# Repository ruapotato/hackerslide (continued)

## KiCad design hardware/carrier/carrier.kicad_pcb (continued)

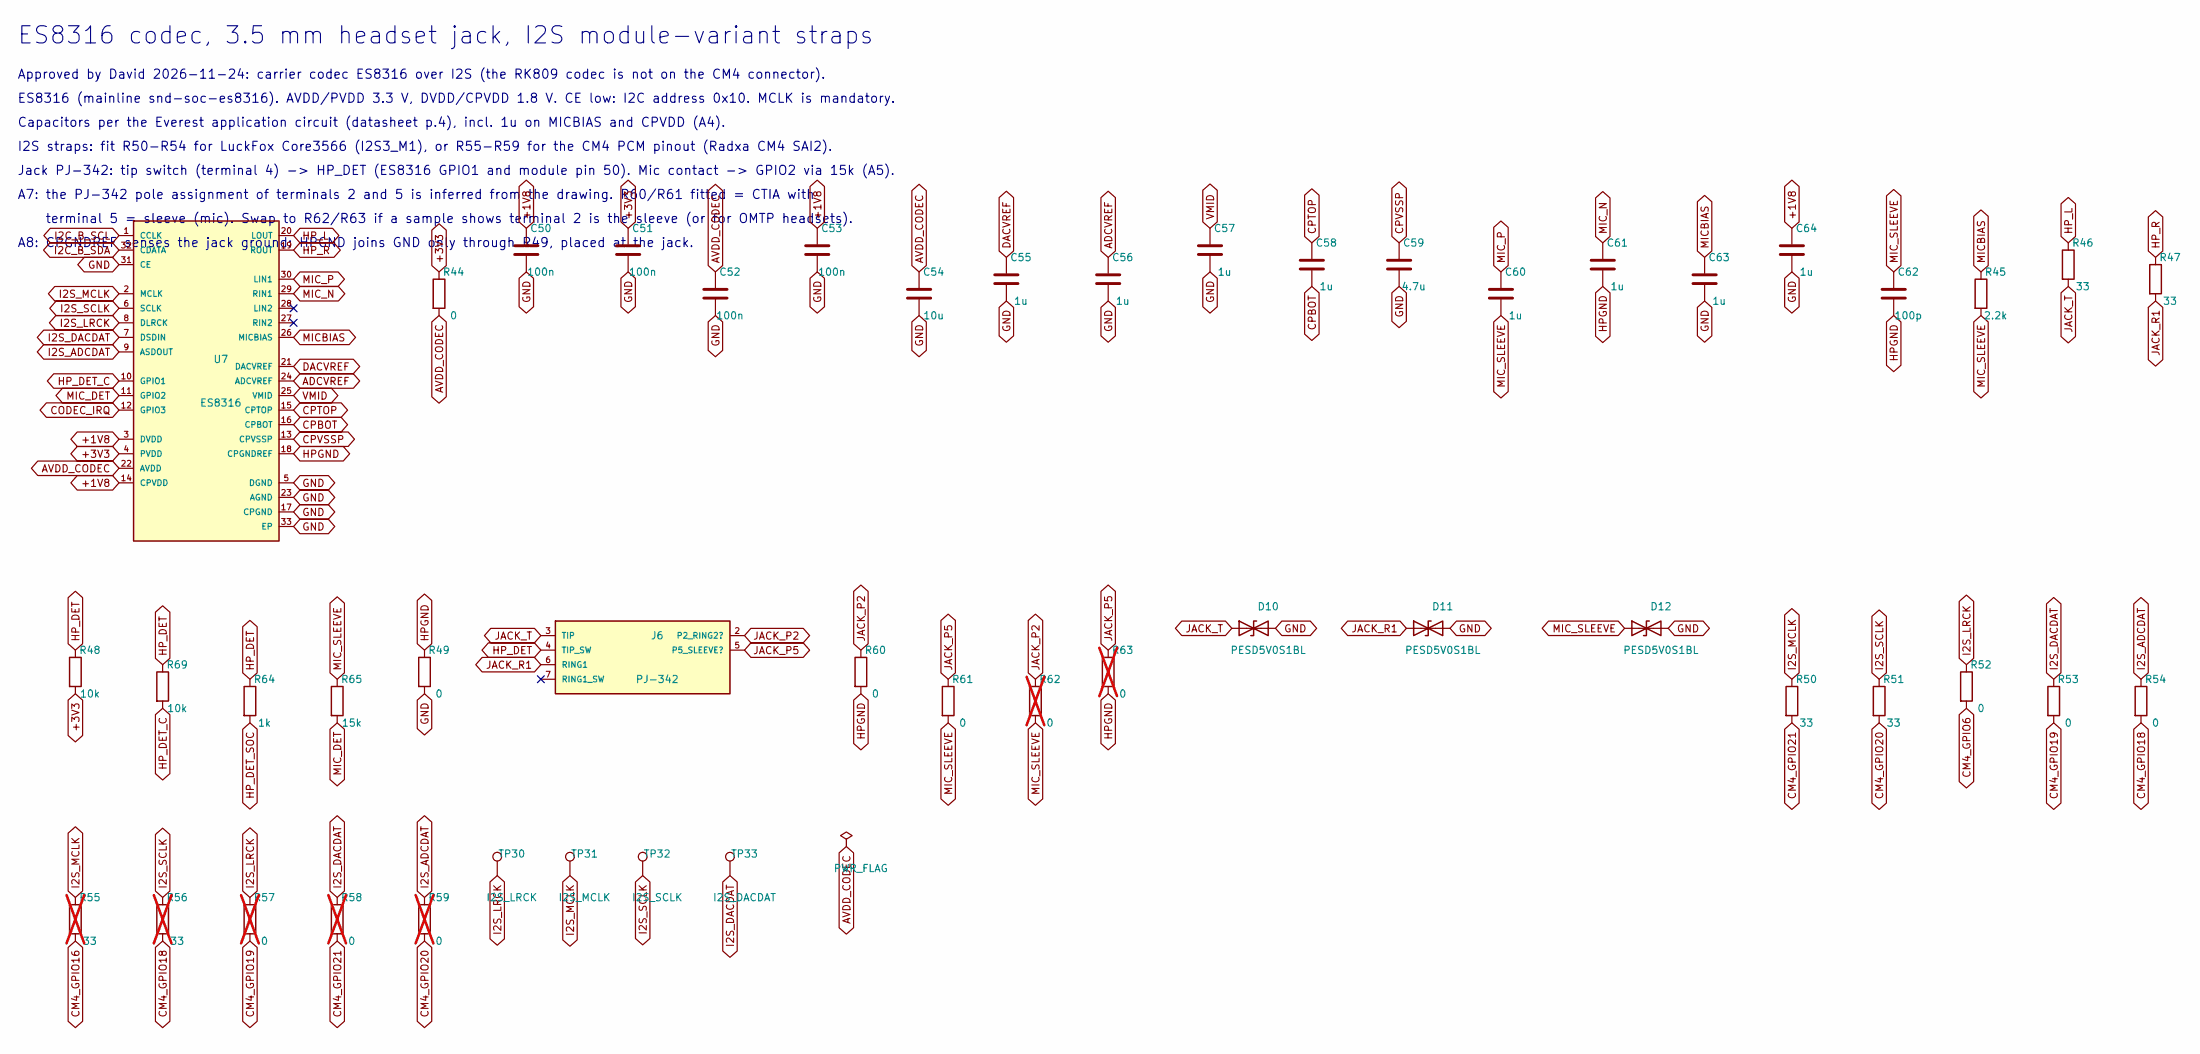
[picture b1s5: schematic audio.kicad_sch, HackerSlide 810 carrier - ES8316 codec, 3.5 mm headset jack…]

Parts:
C50, C51, C52, C53: 100n; C_0402_1005Metric; MPN CL05B104KO5NNNC; LCSC C1525
C54: 10u; C_0603_1608Metric; MPN CL10A106KP8NNNC; LCSC C19702
C55, C56, C57, C58, C60, C61, C63, C64: 1u; C_0402_1005Metric; MPN CL05A105KA5NQNC; LCSC C52923
C59: 4.7u; C_0402_1005Metric; MPN CL05A475MP5NRNC; LCSC C23733
C62: 100p; C_0402_1005Metric; MPN 0402CG101J500NT; LCSC C1546
D10, D11, D12: PESD5V0S1BL; D_SOD-882; MPN PESD5V0S1BL,315; LCSC C84374
J6: PJ-342; Jack_3.5mm_SHOUHAN_PJ-342; MPN PJ-342; LCSC C668606
R44, R49, R52, R53, R54, R60, R61: 0; R_0402_1005Metric; MPN 0402WGF0000TCE; LCSC C17168
R45: 2.2k; R_0402_1005Metric; MPN 0402WGF2201TCE; LCSC C25879
R46, R47, R50, R51: 33; R_0402_1005Metric; MPN 0402WGF330JTCE; LCSC C25105
R48, R69: 10k; R_0402_1005Metric; MPN 0402WGF1002TCE; LCSC C25744
R55, R56: 33; R_0402_1005Metric; MPN 0402WGF330JTCE; LCSC C25105; not fitted
R57, R58, R59, R62, R63: 0; R_0402_1005Metric; MPN 0402WGF0000TCE; LCSC C17168; not fitted
R64: 1k; R_0402_1005Metric; MPN 0402WGF1001TCE; LCSC C11702
R65: 15k; R_0402_1005Metric; MPN 0402WGF1502TCE; LCSC C25756
TP30: I2S_LRCK; TestPoint_Pad_D1.0mm
TP31: I2S_MCLK; TestPoint_Pad_D1.0mm
TP32: I2S_SCLK; TestPoint_Pad_D1.0mm
TP33: I2S_DACDAT; TestPoint_Pad_D1.0mm
U7: ES8316; VQFN-32-1EP_4x4mm_P0.4mm_EP2.8x2.8mm; MPN ES8316; LCSC C365735

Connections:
+1V8: C50.1, C53.1, C64.1, U7.3 (DVDD), U7.14 (CPVDD); also elsewhere on the board
+3V3: C51.1, R44.1, R48.2, U7.4 (PVDD); also elsewhere on the board
ADCVREF: C56.1, U7.24 (ADCVREF)
AVDD_CODEC: C52.1, C54.1, R44.2, U7.22 (AVDD)
CM4_GPIO6: R52.2; also elsewhere on the board
CM4_GPIO16: R55.2; also elsewhere on the board
CM4_GPIO18: R54.2, R56.2; also elsewhere on the board
CM4_GPIO19: R53.2, R57.2; also elsewhere on the board
CM4_GPIO20: R51.2, R59.2; also elsewhere on the board
CM4_GPIO21: R50.2, R58.2; also elsewhere on the board
CODEC_IRQ: U7.12 (GPIO3); also elsewhere on the board
CPBOT: C58.2, U7.16 (CPBOT)
CPTOP: C58.1, U7.15 (CPTOP)
CPVSSP: C59.1, U7.13 (CPVSSP)
DACVREF: C55.1, U7.21 (DACVREF)
GND: C50.2, C51.2, C52.2, C53.2, C54.2, C55.2, C56.2, C57.2, C59.2, C63.2, C64.2, D10.2 (A2), D11.2 (A2), D12.2 (A2), R49.2, U7.5 (DGND), U7.17 (CPGND), U7.23 (AGND), U7.31 (CE), U7.33 (EP); also elsewhere on the board
HPGND: C61.2, C62.2, R49.1, R60.2, R63.2, U7.18 (CPGNDREF)
HP_DET: J6.4 (TIP_SW), R48.1, R64.1, R69.1
HP_DET_C: R69.2, U7.10 (GPIO1)
HP_DET_SOC: R64.2; also elsewhere on the board
HP_L: R46.1, U7.20 (LOUT)
HP_R: R47.1, U7.19 (ROUT)
I2C_B_SCL: U7.1 (CCLK); also elsewhere on the board
I2C_B_SDA: U7.32 (CDATA); also elsewhere on the board
I2S_ADCDAT: R54.1, R59.1, U7.9 (ASDOUT)
I2S_DACDAT: R53.1, R58.1, TP33.1, U7.7 (DSDIN)
I2S_LRCK: R52.1, R57.1, TP30.1, U7.8 (DLRCK)
I2S_MCLK: R50.1, R55.1, TP31.1, U7.2 (MCLK)
I2S_SCLK: R51.1, R56.1, TP32.1, U7.6 (SCLK)
JACK_P2: J6.2 (P2_RING2?), R60.1, R62.1
JACK_P5: J6.5 (P5_SLEEVE?), R61.1, R63.1
JACK_R1: D11.1 (A1), J6.6 (RING1), R47.2
JACK_T: D10.1 (A1), J6.3 (TIP), R46.2
MICBIAS: C63.1, R45.1, U7.26 (MICBIAS)
MIC_DET: R65.2, U7.11 (GPIO2)
MIC_N: C61.1, U7.29 (RIN1)
MIC_P: C60.1, U7.30 (LIN1)
MIC_SLEEVE: C60.2, C62.1, D12.1 (A1), R45.2, R61.2, R62.2, R65.1
VMID: C57.1, U7.25 (VMID)

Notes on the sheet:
ES8316 codec, 3.5 mm headset jack, I2S module-variant straps
Approved by David 2026-11-24: carrier codec ES8316 over I2S (the RK809 codec is not on the CM4 connector).
ES8316 (mainline snd-soc-es8316). AVDD/PVDD 3.3 V, DVDD/CPVDD 1.8 V. CE low: I2C address 0x10. MCLK is mandatory.
Capacitors per the Everest application circuit (datasheet p.4), incl. 1u on MICBIAS and CPVDD (A4).
I2S straps: fit R50-R54 for LuckFox Core3566 (I2S3_M1), or R55-R59 for the CM4 PCM pinout (Radxa CM4 SAI2).
Jack PJ-342: tip switch (terminal 4) -> HP_DET (ES8316 GPIO1 and module pin 50). Mic contact -> GPIO2 via 15k (A5).
A7: the PJ-342 pole assignment of terminals 2 and 5 is inferred from the drawing. R60/R61 fitted = CTIA with
terminal 5 = sleeve (mic). Swap to R62/R63 if a sample shows terminal 2 is the sleeve (or for OMTP headsets).
A8: CPGNDREF senses the jack ground: HPGND joins GND only through R49, placed at the jack.

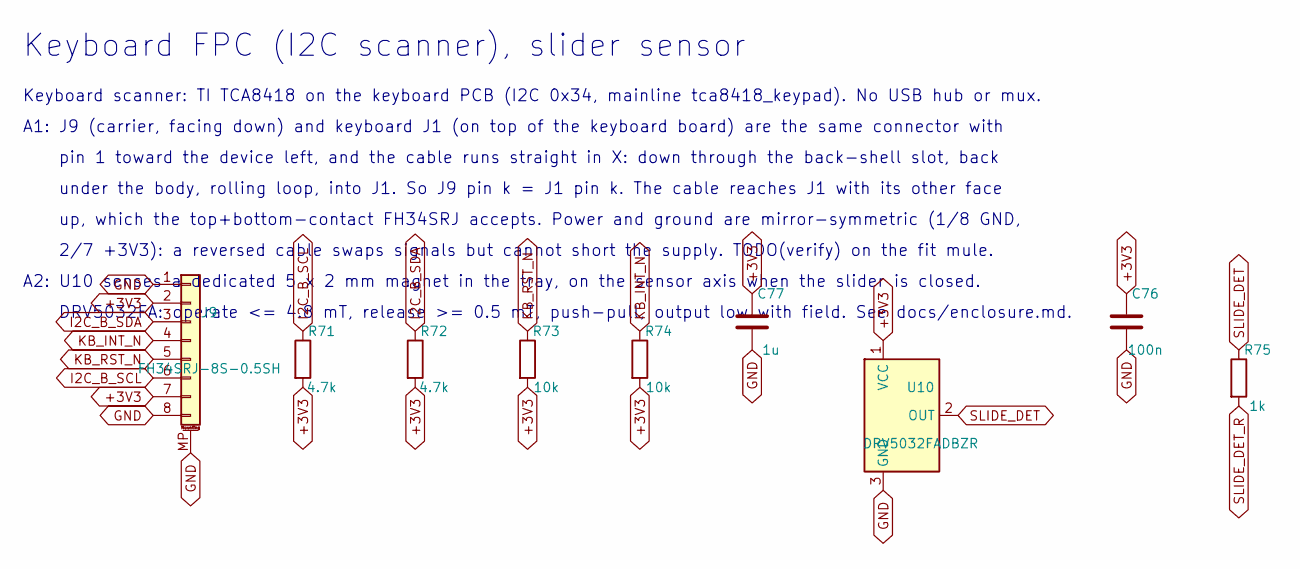
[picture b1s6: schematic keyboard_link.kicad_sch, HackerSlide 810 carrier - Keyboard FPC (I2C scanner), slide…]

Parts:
C76: 100n; C_0402_1005Metric; MPN CL05B104KO5NNNC; LCSC C1525
C77: 1u; C_0402_1005Metric; MPN CL05A105KA5NQNC; LCSC C52923
J9: FH34SRJ-8S-0.5SH; Hirose_FH34SRJ-8S-0.5SH_1x08-1MP_P0.50mm_Horizontal; MPN FH34SRJ-8S-0.5SH(50); LCSC C88372
R71, R72: 4.7k; R_0402_1005Metric; MPN 0402WGF4701TCE; LCSC C25900
R73, R74: 10k; R_0402_1005Metric; MPN 0402WGF1002TCE; LCSC C25744
R75: 1k; R_0402_1005Metric; MPN 0402WGF1001TCE; LCSC C11702
U10: DRV5032FADBZR; SOT-23; MPN DRV5032FADBZR; LCSC C140921

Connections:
+3V3: C76.1, C77.1, J9.2, J9.7, R71.2, R72.2, R73.2, R74.2, U10.1 (VCC); also elsewhere on the board
GND: C76.2, C77.2, J9.1, J9.8, J9.MP (MountPin), U10.3 (GND); also elsewhere on the board
I2C_B_SCL: J9.6, R71.1; also elsewhere on the board
I2C_B_SDA: J9.3, R72.1; also elsewhere on the board
KB_INT_N: J9.4, R74.1; also elsewhere on the board
KB_RST_N: J9.5, R73.1; also elsewhere on the board
SLIDE_DET: R75.1, U10.2 (OUT)
SLIDE_DET_R: R75.2; also elsewhere on the board

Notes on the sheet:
Keyboard FPC (I2C scanner), slider sensor
Keyboard scanner: TI TCA8418 on the keyboard PCB (I2C 0x34, mainline tca8418_keypad). No USB hub or mux.
A1: J9 (carrier, facing down) and keyboard J1 (on top of the keyboard board) are the same connector with
pin 1 toward the device left, and the cable runs straight in X: down through the back-shell slot, back
under the body, rolling loop, into J1. So J9 pin k = J1 pin k. The cable reaches J1 with its other face
up, which the top+bottom-contact FH34SRJ accepts. Power and ground are mirror-symmetric (1/8 GND,
2/7 +3V3): a reversed cable swaps signals but cannot short the supply. TODO(verify) on the fit mule.
A2: U10 senses a dedicated 5 x 2 mm magnet in the tray, on the sensor axis when the slider is closed.
DRV5032FA: operate <= 4.8 mT, release >= 0.5 mT, push-pull, output low with field. See docs/enclosure.md.

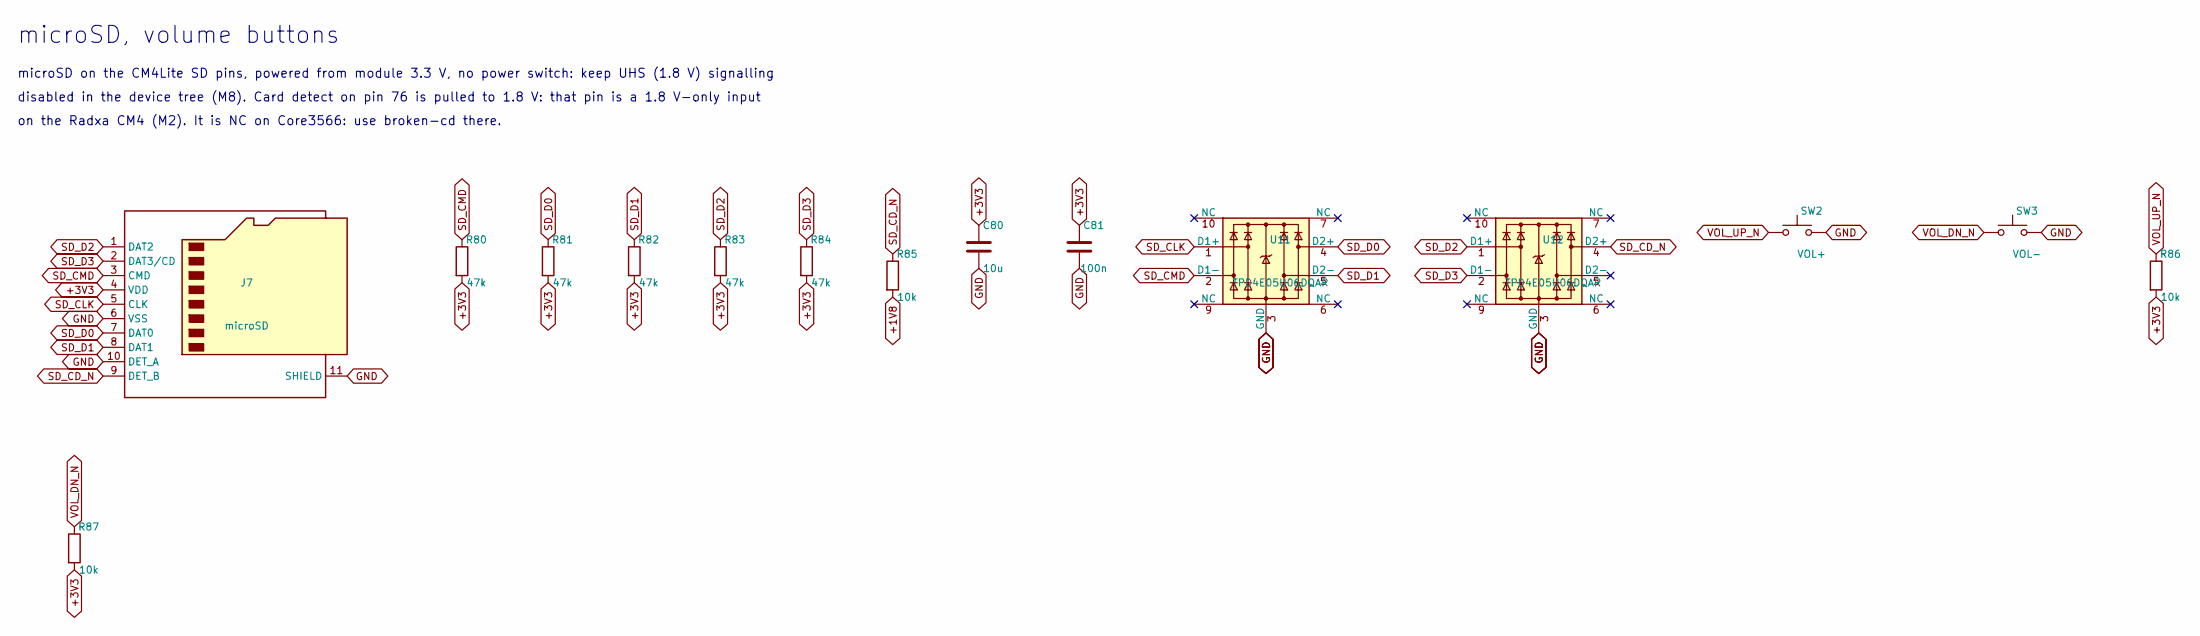
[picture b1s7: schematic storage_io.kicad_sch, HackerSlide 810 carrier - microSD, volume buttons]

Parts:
C80: 10u; C_0603_1608Metric; MPN CL10A106KP8NNNC; LCSC C19702
C81: 100n; C_0402_1005Metric; MPN CL05B104KO5NNNC; LCSC C1525
J7: microSD; microSD_HC_Molex_104031-0811; MPN 1040310811; LCSC C585350
R80, R81, R82, R83, R84: 47k; R_0402_1005Metric; MPN 0402WGF4702TCE; LCSC C25792
R85, R86, R87: 10k; R_0402_1005Metric; MPN 0402WGF1002TCE; LCSC C25744
SW2: VOL+; SW_SPST_EVQP7C; MPN EVQP7C01P; LCSC C388883
SW3: VOL-; SW_SPST_EVQP7C; MPN EVQP7C01P; LCSC C388883
U11, U12: TPD4E05U06DQAR; USON-10_2.5x1.0mm_P0.5mm; MPN TPD4E05U06DQAR; LCSC C138714

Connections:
+1V8: R85.2; also elsewhere on the board
+3V3: C80.1, C81.1, J7.4 (VDD), R80.2, R81.2, R82.2, R83.2, R84.2, R86.2, R87.2; also elsewhere on the board
GND: C80.2, C81.2, J7.6 (VSS), J7.10 (DET_A), J7.11 (SHIELD), SW2.2, SW3.2, U11.3 (GND), U11.8 (GND), U12.3 (GND), U12.8 (GND); also elsewhere on the board
SD_CD_N: J7.9 (DET_B), R85.1, U12.4 (D2+); also elsewhere on the board
SD_CLK: J7.5 (CLK), U11.1 (D1+); also elsewhere on the board
SD_CMD: J7.3 (CMD), R80.1, U11.2 (D1-); also elsewhere on the board
SD_D0: J7.7 (DAT0), R81.1, U11.4 (D2+); also elsewhere on the board
SD_D1: J7.8 (DAT1), R82.1, U11.5 (D2-); also elsewhere on the board
SD_D2: J7.1 (DAT2), R83.1, U12.1 (D1+); also elsewhere on the board
SD_D3: J7.2 (DAT3/CD), R84.1, U12.2 (D1-); also elsewhere on the board
VOL_DN_N: R87.1, SW3.1; also elsewhere on the board
VOL_UP_N: R86.1, SW2.1; also elsewhere on the board

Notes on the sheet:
microSD, volume buttons
microSD on the CM4Lite SD pins, powered from module 3.3 V, no power switch: keep UHS (1.8 V) signalling
disabled in the device tree (M8). Card detect on pin 76 is pulled to 1.8 V: that pin is a 1.8 V-only input
on the Radxa CM4 (M2). It is NC on Core3566: use broken-cd there.

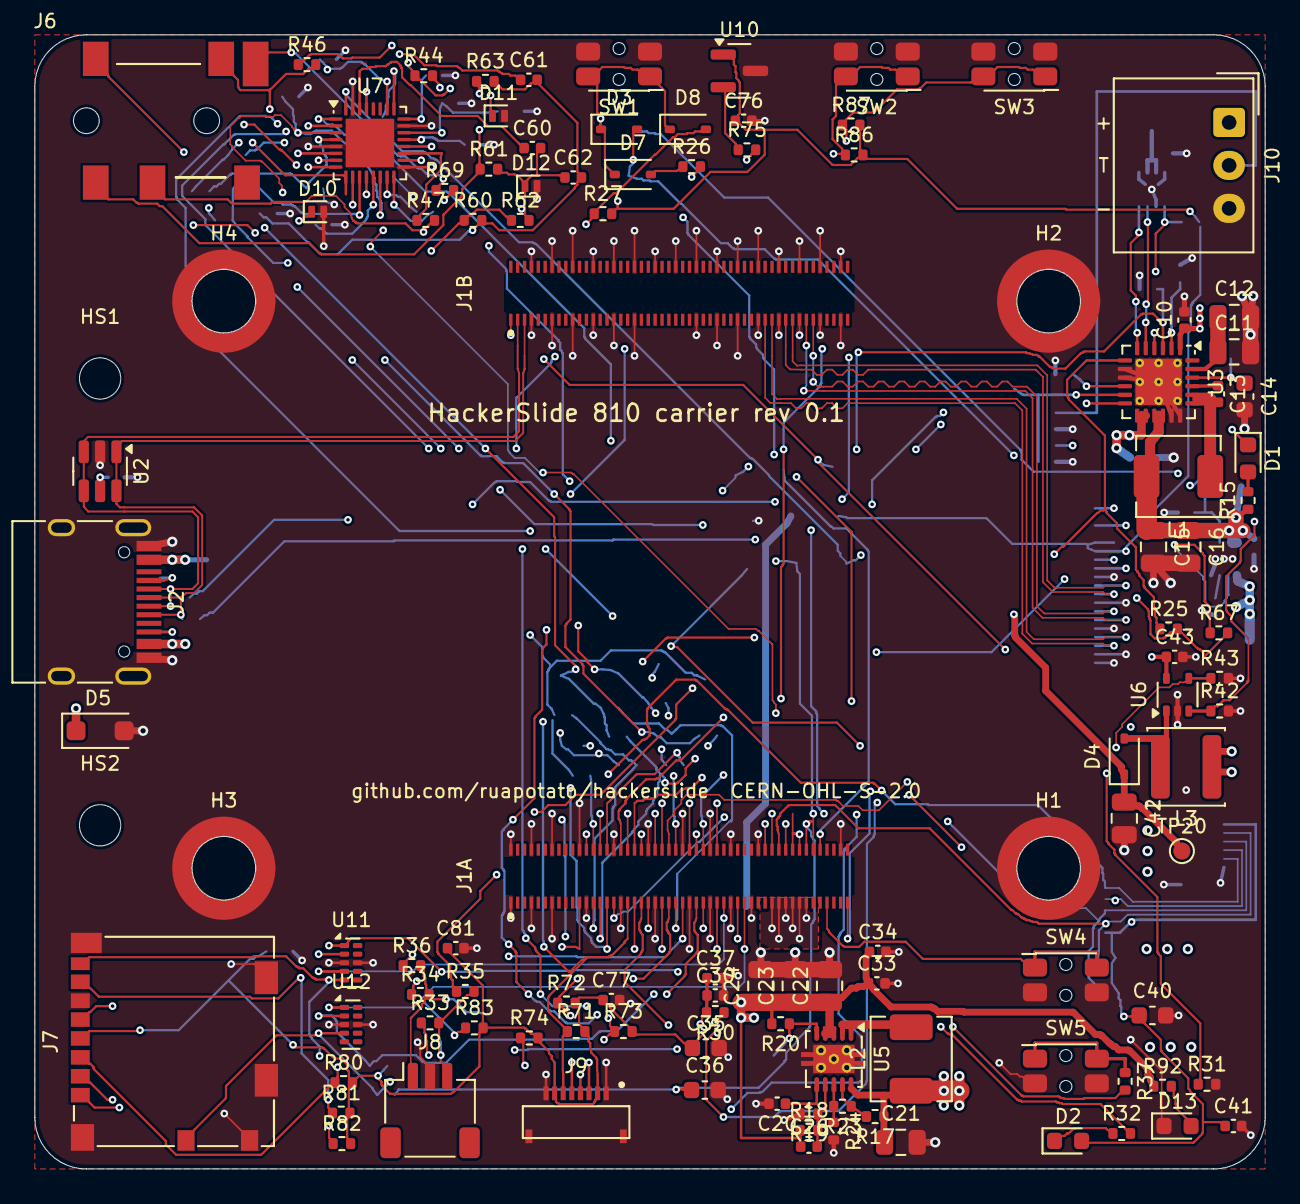
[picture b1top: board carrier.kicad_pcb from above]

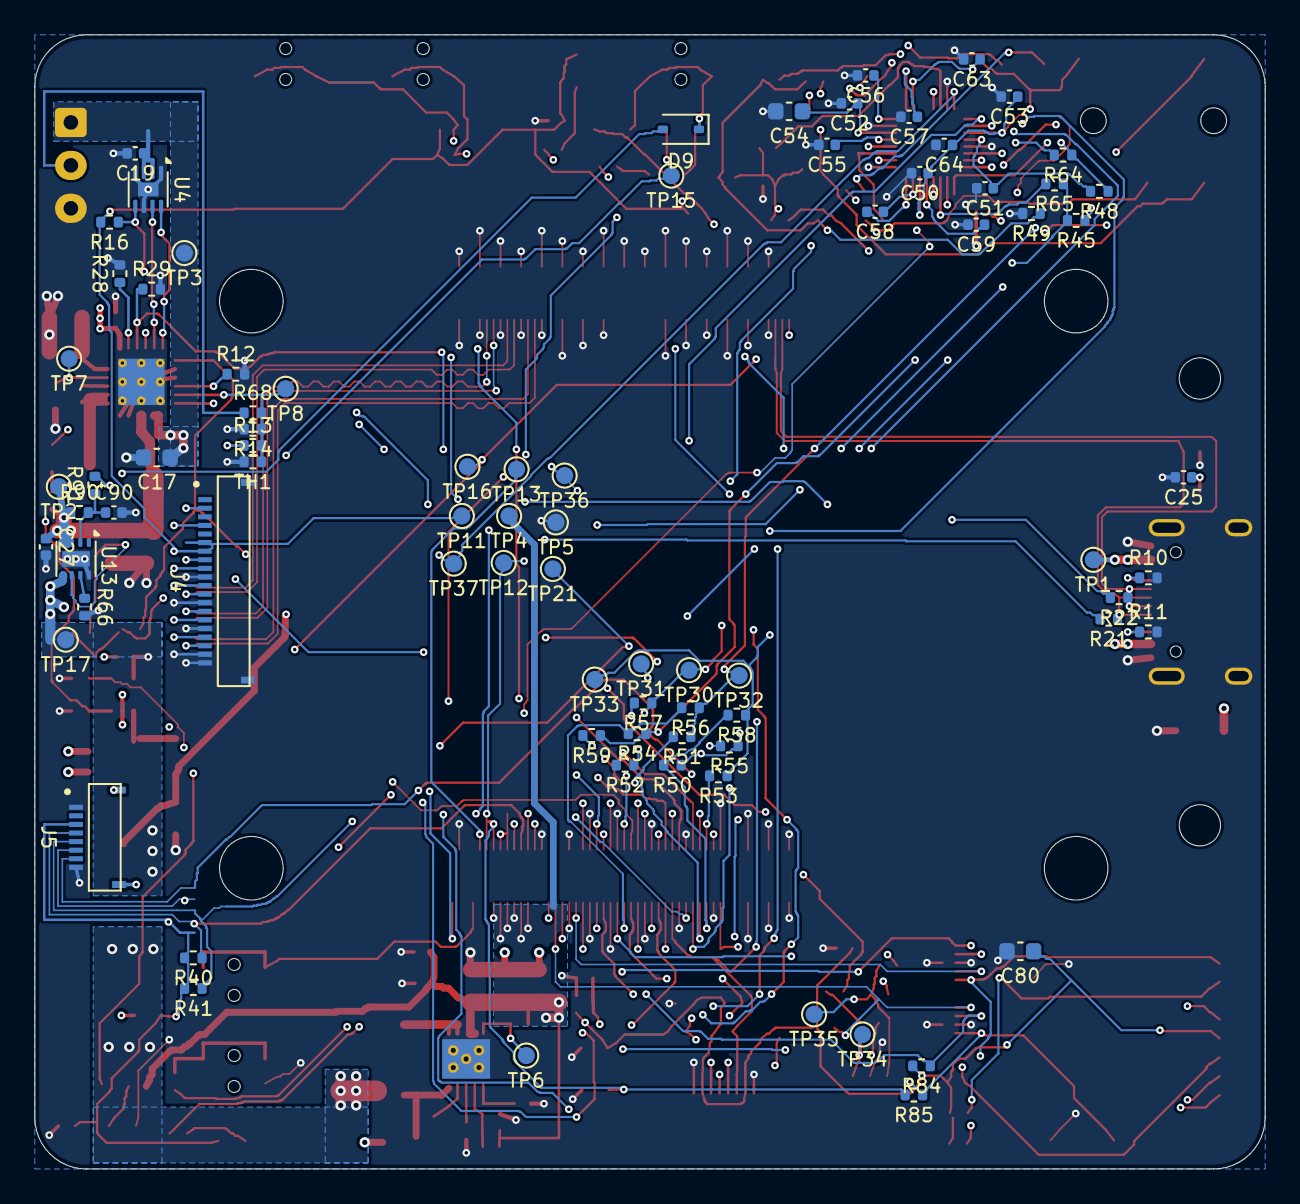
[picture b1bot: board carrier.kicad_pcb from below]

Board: 4 copper layers, 71.6 x 66.0 mm, 192 parts (80 on the bottom side), 120 nets.

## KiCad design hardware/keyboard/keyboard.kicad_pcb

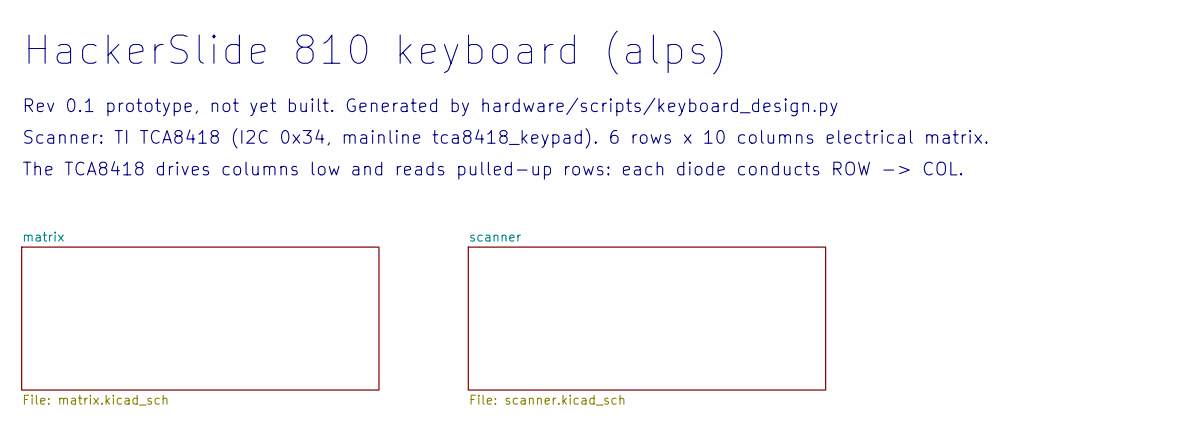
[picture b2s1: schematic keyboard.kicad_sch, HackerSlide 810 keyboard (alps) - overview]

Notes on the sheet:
HackerSlide 810 keyboard (alps)
Rev 0.1 prototype, not yet built. Generated by hardware/scripts/keyboard_design.py
Scanner: TI TCA8418 (I2C 0x34, mainline tca8418_keypad). 6 rows x 10 columns electrical matrix.
The TCA8418 drives columns low and reads pulled-up rows: each diode conducts ROW -> COL.

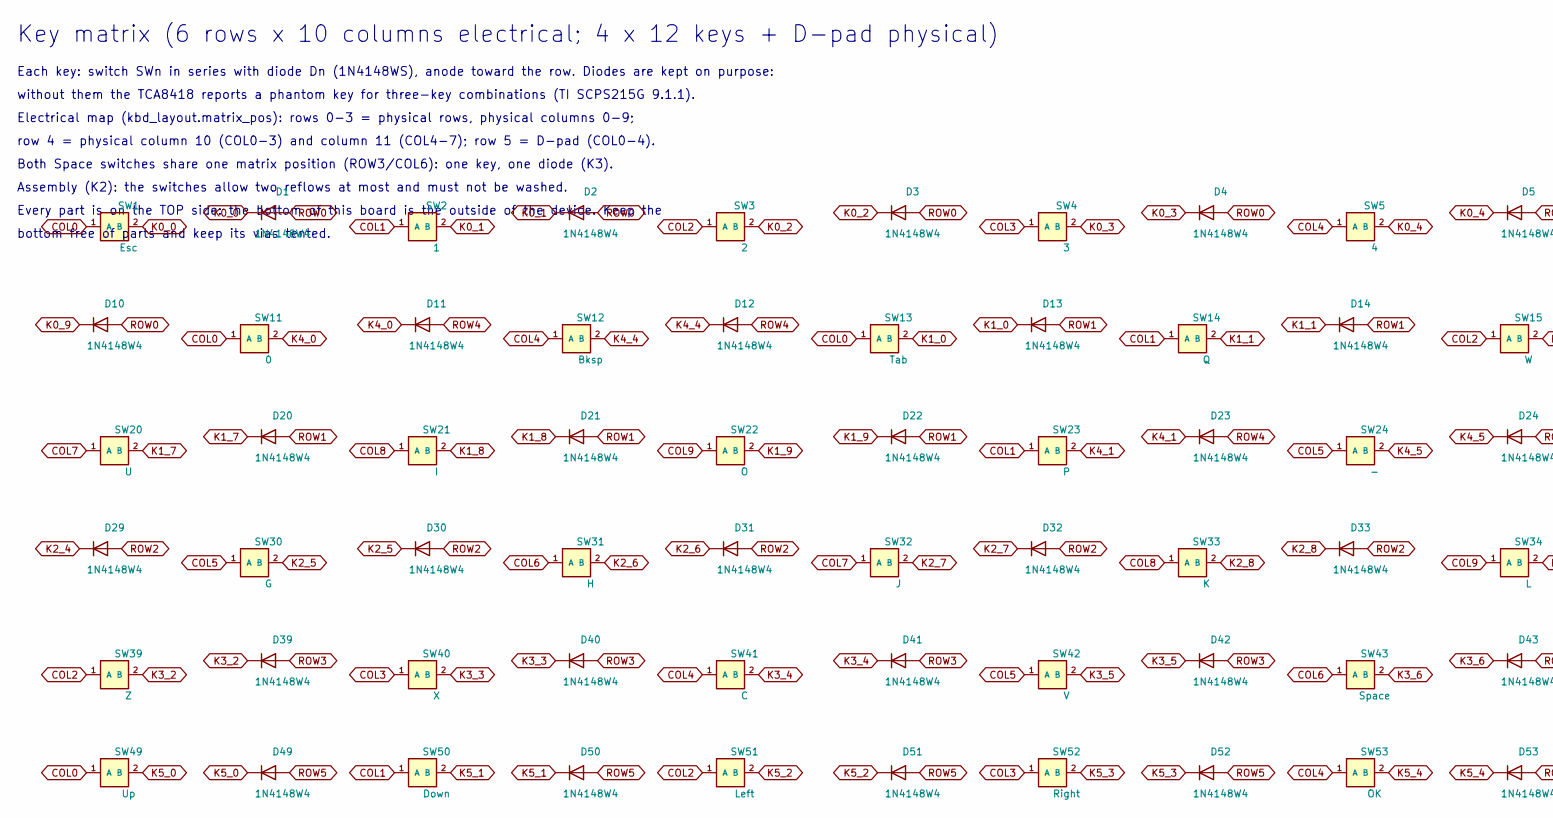
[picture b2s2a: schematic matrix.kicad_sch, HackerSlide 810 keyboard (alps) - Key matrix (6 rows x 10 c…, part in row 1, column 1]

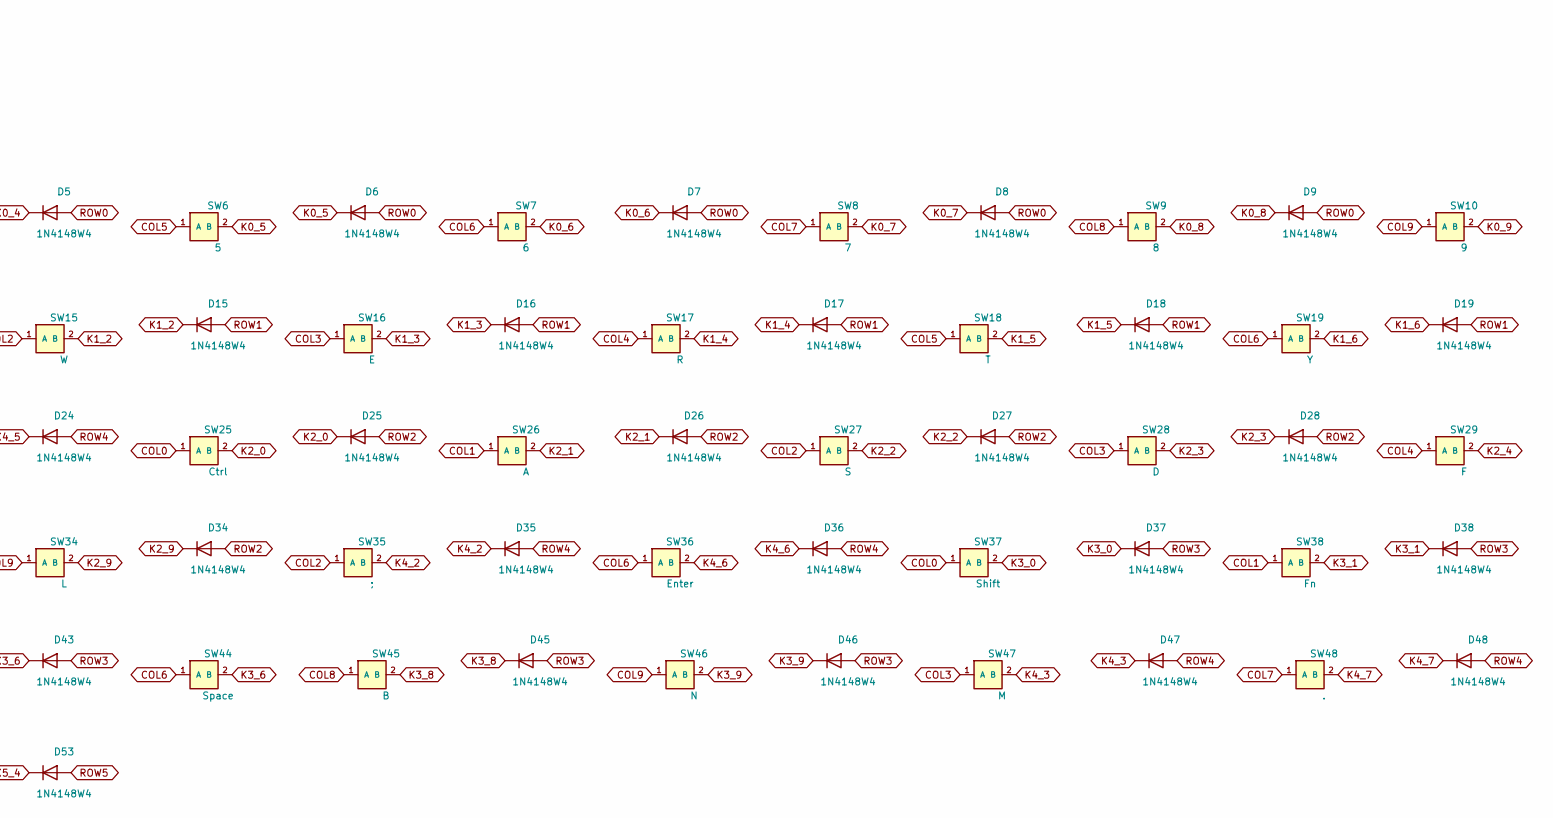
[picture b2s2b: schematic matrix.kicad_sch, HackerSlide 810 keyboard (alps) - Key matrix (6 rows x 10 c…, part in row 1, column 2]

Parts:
D1, D2, D3, D4, D5, D6, D7, D8, D9, D10, D11, D12, D13, D14, D15, D16, D17, D18, D19, D20, D21, D22, D23, D24, D25, D26, D27, D28, D29, D30, D31, D32, D33, D34, D35, D36, D37, D38, D39, D40, D41, D42, D43, D45, D46, D47, D48, D49, D50, D51, D52, D53: 1N4148W4; D_SOD-882; MPN 1N4148W4; LCSC C42432416
SW1: Esc; SW_Alps_SKSWCFE010_3x2mm; MPN SKSWCFE010; LCSC C255576
SW2: 1; SW_Alps_SKSWCFE010_3x2mm; MPN SKSWCFE010; LCSC C255576
SW3: 2; SW_Alps_SKSWCFE010_3x2mm; MPN SKSWCFE010; LCSC C255576
SW4: 3; SW_Alps_SKSWCFE010_3x2mm; MPN SKSWCFE010; LCSC C255576
SW5: 4; SW_Alps_SKSWCFE010_3x2mm; MPN SKSWCFE010; LCSC C255576
SW6: 5; SW_Alps_SKSWCFE010_3x2mm; MPN SKSWCFE010; LCSC C255576
SW7: 6; SW_Alps_SKSWCFE010_3x2mm; MPN SKSWCFE010; LCSC C255576
SW8: 7; SW_Alps_SKSWCFE010_3x2mm; MPN SKSWCFE010; LCSC C255576
SW9: 8; SW_Alps_SKSWCFE010_3x2mm; MPN SKSWCFE010; LCSC C255576
SW10: 9; SW_Alps_SKSWCFE010_3x2mm; MPN SKSWCFE010; LCSC C255576
SW11: 0; SW_Alps_SKSWCFE010_3x2mm; MPN SKSWCFE010; LCSC C255576
SW12: Bksp; SW_Alps_SKSWCFE010_3x2mm; MPN SKSWCFE010; LCSC C255576
SW13: Tab; SW_Alps_SKSWCFE010_3x2mm; MPN SKSWCFE010; LCSC C255576
SW14: Q; SW_Alps_SKSWCFE010_3x2mm; MPN SKSWCFE010; LCSC C255576
SW15: W; SW_Alps_SKSWCFE010_3x2mm; MPN SKSWCFE010; LCSC C255576
SW16: E; SW_Alps_SKSWCFE010_3x2mm; MPN SKSWCFE010; LCSC C255576
SW17: R; SW_Alps_SKSWCFE010_3x2mm; MPN SKSWCFE010; LCSC C255576
SW18: T; SW_Alps_SKSWCFE010_3x2mm; MPN SKSWCFE010; LCSC C255576
SW19: Y; SW_Alps_SKSWCFE010_3x2mm; MPN SKSWCFE010; LCSC C255576
SW20: U; SW_Alps_SKSWCFE010_3x2mm; MPN SKSWCFE010; LCSC C255576
SW21: I; SW_Alps_SKSWCFE010_3x2mm; MPN SKSWCFE010; LCSC C255576
SW22: O; SW_Alps_SKSWCFE010_3x2mm; MPN SKSWCFE010; LCSC C255576
SW23: P; SW_Alps_SKSWCFE010_3x2mm; MPN SKSWCFE010; LCSC C255576
SW24: -; SW_Alps_SKSWCFE010_3x2mm; MPN SKSWCFE010; LCSC C255576
SW25: Ctrl; SW_Alps_SKSWCFE010_3x2mm; MPN SKSWCFE010; LCSC C255576
SW26: A; SW_Alps_SKSWCFE010_3x2mm; MPN SKSWCFE010; LCSC C255576
SW27: S; SW_Alps_SKSWCFE010_3x2mm; MPN SKSWCFE010; LCSC C255576
SW28: D; SW_Alps_SKSWCFE010_3x2mm; MPN SKSWCFE010; LCSC C255576
SW29: F; SW_Alps_SKSWCFE010_3x2mm; MPN SKSWCFE010; LCSC C255576
SW30: G; SW_Alps_SKSWCFE010_3x2mm; MPN SKSWCFE010; LCSC C255576
SW31: H; SW_Alps_SKSWCFE010_3x2mm; MPN SKSWCFE010; LCSC C255576
SW32: J; SW_Alps_SKSWCFE010_3x2mm; MPN SKSWCFE010; LCSC C255576
SW33: K; SW_Alps_SKSWCFE010_3x2mm; MPN SKSWCFE010; LCSC C255576
SW34: L; SW_Alps_SKSWCFE010_3x2mm; MPN SKSWCFE010; LCSC C255576
SW35: ;; SW_Alps_SKSWCFE010_3x2mm; MPN SKSWCFE010; LCSC C255576
SW36: Enter; SW_Alps_SKSWCFE010_3x2mm; MPN SKSWCFE010; LCSC C255576
SW37: Shift; SW_Alps_SKSWCFE010_3x2mm; MPN SKSWCFE010; LCSC C255576
SW38: Fn; SW_Alps_SKSWCFE010_3x2mm; MPN SKSWCFE010; LCSC C255576
SW39: Z; SW_Alps_SKSWCFE010_3x2mm; MPN SKSWCFE010; LCSC C255576
SW40: X; SW_Alps_SKSWCFE010_3x2mm; MPN SKSWCFE010; LCSC C255576
SW41: C; SW_Alps_SKSWCFE010_3x2mm; MPN SKSWCFE010; LCSC C255576
SW42: V; SW_Alps_SKSWCFE010_3x2mm; MPN SKSWCFE010; LCSC C255576
SW43, SW44: Space; SW_Alps_SKSWCFE010_3x2mm; MPN SKSWCFE010; LCSC C255576
SW45: B; SW_Alps_SKSWCFE010_3x2mm; MPN SKSWCFE010; LCSC C255576
SW46: N; SW_Alps_SKSWCFE010_3x2mm; MPN SKSWCFE010; LCSC C255576
SW47: M; SW_Alps_SKSWCFE010_3x2mm; MPN SKSWCFE010; LCSC C255576
SW48: .; SW_Alps_SKSWCFE010_3x2mm; MPN SKSWCFE010; LCSC C255576
SW49: Up; SW_Alps_SKSWCFE010_3x2mm; MPN SKSWCFE010; LCSC C255576
SW50: Down; SW_Alps_SKSWCFE010_3x2mm; MPN SKSWCFE010; LCSC C255576
SW51: Left; SW_Alps_SKSWCFE010_3x2mm; MPN SKSWCFE010; LCSC C255576
SW52: Right; SW_Alps_SKSWCFE010_3x2mm; MPN SKSWCFE010; LCSC C255576
SW53: OK; SW_Alps_SKSWCFE010_3x2mm; MPN SKSWCFE010; LCSC C255576

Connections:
COL0: SW1.1 (A), SW11.1 (A), SW13.1 (A), SW25.1 (A), SW37.1 (A), SW49.1 (A); also elsewhere on the board
COL1: SW2.1 (A), SW14.1 (A), SW23.1 (A), SW26.1 (A), SW38.1 (A), SW50.1 (A); also elsewhere on the board
COL2: SW3.1 (A), SW15.1 (A), SW27.1 (A), SW35.1 (A), SW39.1 (A), SW51.1 (A); also elsewhere on the board
COL3: SW4.1 (A), SW16.1 (A), SW28.1 (A), SW40.1 (A), SW47.1 (A), SW52.1 (A); also elsewhere on the board
COL4: SW5.1 (A), SW12.1 (A), SW17.1 (A), SW29.1 (A), SW41.1 (A), SW53.1 (A); also elsewhere on the board
COL5: SW6.1 (A), SW18.1 (A), SW24.1 (A), SW30.1 (A), SW42.1 (A); also elsewhere on the board
COL6: SW7.1 (A), SW19.1 (A), SW31.1 (A), SW36.1 (A), SW43.1 (A), SW44.1 (A); also elsewhere on the board
COL7: SW8.1 (A), SW20.1 (A), SW32.1 (A), SW48.1 (A); also elsewhere on the board
COL8: SW9.1 (A), SW21.1 (A), SW33.1 (A), SW45.1 (A); also elsewhere on the board
COL9: SW10.1 (A), SW22.1 (A), SW34.1 (A), SW46.1 (A); also elsewhere on the board
K0_0: D1.1 (K), SW1.2 (B)
K0_1: D2.1 (K), SW2.2 (B)
K0_2: D3.1 (K), SW3.2 (B)
K0_3: D4.1 (K), SW4.2 (B)
K0_4: D5.1 (K), SW5.2 (B)
K0_5: D6.1 (K), SW6.2 (B)
K0_6: D7.1 (K), SW7.2 (B)
K0_7: D8.1 (K), SW8.2 (B)
K0_8: D9.1 (K), SW9.2 (B)
K0_9: D10.1 (K), SW10.2 (B)
K1_0: D13.1 (K), SW13.2 (B)
K1_1: D14.1 (K), SW14.2 (B)
K1_2: D15.1 (K), SW15.2 (B)
K1_3: D16.1 (K), SW16.2 (B)
K1_4: D17.1 (K), SW17.2 (B)
K1_5: D18.1 (K), SW18.2 (B)
K1_6: D19.1 (K), SW19.2 (B)
K1_7: D20.1 (K), SW20.2 (B)
K1_8: D21.1 (K), SW21.2 (B)
K1_9: D22.1 (K), SW22.2 (B)
K2_0: D25.1 (K), SW25.2 (B)
K2_1: D26.1 (K), SW26.2 (B)
K2_2: D27.1 (K), SW27.2 (B)
K2_3: D28.1 (K), SW28.2 (B)
K2_4: D29.1 (K), SW29.2 (B)
K2_5: D30.1 (K), SW30.2 (B)
K2_6: D31.1 (K), SW31.2 (B)
K2_7: D32.1 (K), SW32.2 (B)
K2_8: D33.1 (K), SW33.2 (B)
K2_9: D34.1 (K), SW34.2 (B)
K3_0: D37.1 (K), SW37.2 (B)
K3_1: D38.1 (K), SW38.2 (B)
K3_2: D39.1 (K), SW39.2 (B)
K3_3: D40.1 (K), SW40.2 (B)
K3_4: D41.1 (K), SW41.2 (B)
K3_5: D42.1 (K), SW42.2 (B)
K3_6: D43.1 (K), SW43.2 (B), SW44.2 (B)
K3_8: D45.1 (K), SW45.2 (B)
K3_9: D46.1 (K), SW46.2 (B)
K4_0: D11.1 (K), SW11.2 (B)
K4_1: D23.1 (K), SW23.2 (B)
K4_2: D35.1 (K), SW35.2 (B)
K4_3: D47.1 (K), SW47.2 (B)
K4_4: D12.1 (K), SW12.2 (B)
K4_5: D24.1 (K), SW24.2 (B)
K4_6: D36.1 (K), SW36.2 (B)
K4_7: D48.1 (K), SW48.2 (B)
K5_0: D49.1 (K), SW49.2 (B)
K5_1: D50.1 (K), SW50.2 (B)
K5_2: D51.1 (K), SW51.2 (B)
K5_3: D52.1 (K), SW52.2 (B)
K5_4: D53.1 (K), SW53.2 (B)
ROW0: D1.2 (A), D2.2 (A), D3.2 (A), D4.2 (A), D5.2 (A), D6.2 (A), D7.2 (A), D8.2 (A), D9.2 (A), D10.2 (A); also elsewhere on the board
ROW1: D13.2 (A), D14.2 (A), D15.2 (A), D16.2 (A), D17.2 (A), D18.2 (A), D19.2 (A), D20.2 (A), D21.2 (A), D22.2 (A); also elsewhere on the board
ROW2: D25.2 (A), D26.2 (A), D27.2 (A), D28.2 (A), D29.2 (A), D30.2 (A), D31.2 (A), D32.2 (A), D33.2 (A), D34.2 (A); also elsewhere on the board
ROW3: D37.2 (A), D38.2 (A), D39.2 (A), D40.2 (A), D41.2 (A), D42.2 (A), D43.2 (A), D45.2 (A), D46.2 (A); also elsewhere on the board
ROW4: D11.2 (A), D12.2 (A), D23.2 (A), D24.2 (A), D35.2 (A), D36.2 (A), D47.2 (A), D48.2 (A); also elsewhere on the board
ROW5: D49.2 (A), D50.2 (A), D51.2 (A), D52.2 (A), D53.2 (A); also elsewhere on the board

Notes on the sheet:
Key matrix (6 rows x 10 columns electrical; 4 x 12 keys + D-pad physical)
Each key: switch SWn in series with diode Dn (1N4148WS), anode toward the row. Diodes are kept on purpose:
without them the TCA8418 reports a phantom key for three-key combinations (TI SCPS215G 9.1.1).
Electrical map (kbd_layout.matrix_pos): rows 0-3 = physical rows, physical columns 0-9;
row 4 = physical column 10 (COL0-3) and column 11 (COL4-7); row 5 = D-pad (COL0-4).
Both Space switches share one matrix position (ROW3/COL6): one key, one diode (K3).
Assembly (K2): the switches allow two reflows at most and must not be washed.
Every part is on the TOP side: the bottom of this board is the outside of the device. Keep the
bottom free of parts and keep its vias tented.

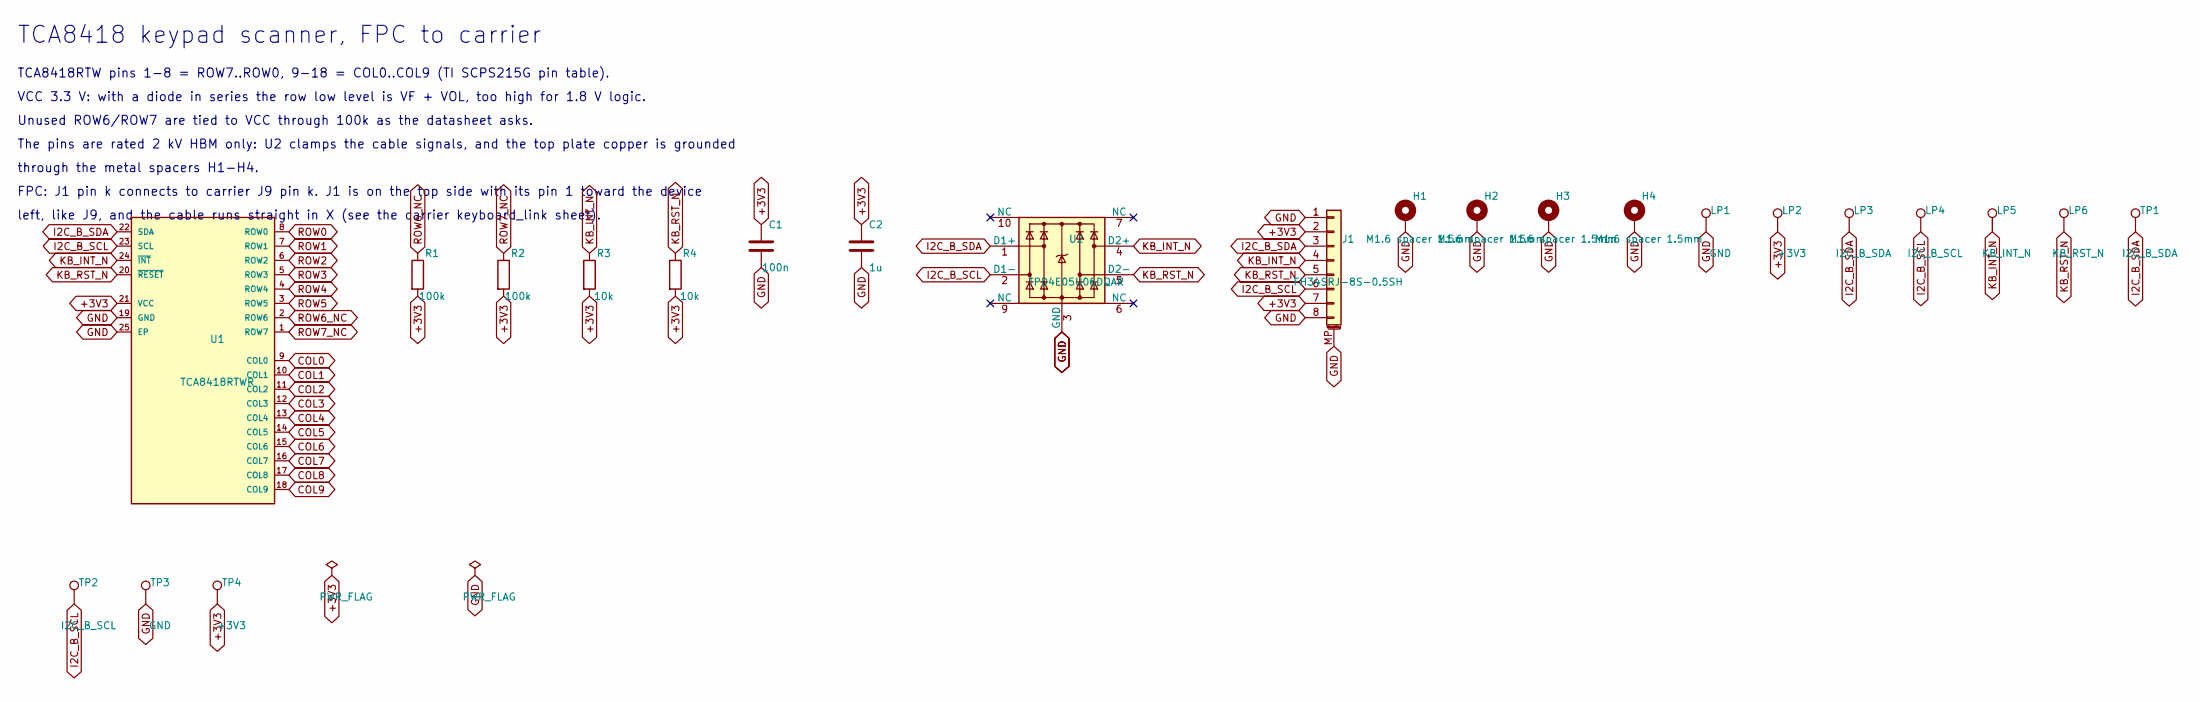
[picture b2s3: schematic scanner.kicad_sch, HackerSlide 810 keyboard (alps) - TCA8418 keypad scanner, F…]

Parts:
C1: 100n; C_0402_1005Metric; MPN CL05B104KO5NNNC; LCSC C1525
C2: 1u; C_0402_1005Metric; MPN CL05A105KA5NQNC; LCSC C52923
H1, H2, H3, H4: M1.6 spacer 1.5mm; Mounting_Wuerth_WA-SMSI-M1.6_H1.5mm_9774015633; MPN 9774015633R
J1: FH34SRJ-8S-0.5SH; Hirose_FH34SRJ-8S-0.5SH_1x08-1MP_P0.50mm_Horizontal; MPN FH34SRJ-8S-0.5SH(50); LCSC C88372
LP1: GND; ContactPad_2x4mm
LP2: +3V3; ContactPad_2x4mm
LP3: I2C_B_SDA; ContactPad_2x4mm
LP4: I2C_B_SCL; ContactPad_2x4mm
LP5: KB_INT_N; ContactPad_2x4mm
LP6: KB_RST_N; ContactPad_2x4mm
R1, R2: 100k; R_0402_1005Metric; MPN 0402WGF1003TCE; LCSC C25741
R3, R4: 10k; R_0402_1005Metric; MPN 0402WGF1002TCE; LCSC C25744
TP1: I2C_B_SDA; TestPoint_Pad_D1.0mm
TP2: I2C_B_SCL; TestPoint_Pad_D1.0mm
TP3: GND; TestPoint_Pad_D1.0mm
TP4: +3V3; TestPoint_Pad_D1.0mm
U1: TCA8418RTWR; WQFN-24-1EP_4x4mm_P0.5mm_EP2.45x2.45mm; MPN TCA8418RTWR; LCSC C138713
U2: TPD4E05U06DQAR; USON-10_2.5x1.0mm_P0.5mm; MPN TPD4E05U06DQAR; LCSC C138714

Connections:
+3V3: C1.1, C2.1, J1.2, J1.7, LP2.1, R1.2, R2.2, R3.2, R4.2, TP4.1, U1.21 (VCC)
COL0: U1.9 (COL0); also elsewhere on the board
COL1: U1.10 (COL1); also elsewhere on the board
COL2: U1.11 (COL2); also elsewhere on the board
COL3: U1.12 (COL3); also elsewhere on the board
COL4: U1.13 (COL4); also elsewhere on the board
COL5: U1.14 (COL5); also elsewhere on the board
COL6: U1.15 (COL6); also elsewhere on the board
COL7: U1.16 (COL7); also elsewhere on the board
COL8: U1.17 (COL8); also elsewhere on the board
COL9: U1.18 (COL9); also elsewhere on the board
GND: C1.2, C2.2, H1.1, H2.1, H3.1, H4.1, J1.1, J1.8, J1.MP (MountPin), LP1.1, TP3.1, U1.19 (GND), U1.25 (EP), U2.3 (GND), U2.8 (GND)
I2C_B_SCL: J1.6, LP4.1, TP2.1, U1.23 (SCL), U2.2 (D1-)
I2C_B_SDA: J1.3, LP3.1, TP1.1, U1.22 (SDA), U2.1 (D1+)
KB_INT_N: J1.4, LP5.1, R3.1, U1.24 (~INT), U2.4 (D2+)
KB_RST_N: J1.5, LP6.1, R4.1, U1.20 (~RESET), U2.5 (D2-)
ROW0: U1.8 (ROW0); also elsewhere on the board
ROW1: U1.7 (ROW1); also elsewhere on the board
ROW2: U1.6 (ROW2); also elsewhere on the board
ROW3: U1.5 (ROW3); also elsewhere on the board
ROW4: U1.4 (ROW4); also elsewhere on the board
ROW5: U1.3 (ROW5); also elsewhere on the board
ROW6_NC: R1.1, U1.2 (ROW6)
ROW7_NC: R2.1, U1.1 (ROW7)

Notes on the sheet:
TCA8418 keypad scanner, FPC to carrier
TCA8418RTW pins 1-8 = ROW7..ROW0, 9-18 = COL0..COL9 (TI SCPS215G pin table).
VCC 3.3 V: with a diode in series the row low level is VF + VOL, too high for 1.8 V logic.
Unused ROW6/ROW7 are tied to VCC through 100k as the datasheet asks.
The pins are rated 2 kV HBM only: U2 clamps the cable signals, and the top plate copper is grounded
through the metal spacers H1-H4.
FPC: J1 pin k connects to carrier J9 pin k. J1 is on the top side with its pin 1 toward the device
left, like J9, and the cable runs straight in X (see the carrier keyboard_link sheet).
